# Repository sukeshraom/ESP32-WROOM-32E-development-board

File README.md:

# ESP32-WROOM-32E Development Board (Arduino UNO Form Factor)

A compact **ESP32-WROOM-32E Development Board** designed in the **Arduino UNO form factor** with a **USB Type-C** interface and **CH340C USB-to-UART** converter. The board combines the versatility of the ESP32 with the familiar Arduino UNO header layout, making it suitable for rapid prototyping and shield-based development.

[View PCB in Kicanvas](https://kicanvas.org/?repo=https%3A%2F%2Fgithub.com%2Fsamuk%2FESP32-WROOM-32E-development-board%2Ftree%2Fmain%2FKicad)
---

## Features

- ESP32-WROOM-32E module
- Arduino UNO compatible form factor
- USB Type-C connector for power and programming
- CH340C USB-to-UART interface
- Auto Reset and Auto Boot circuitry
- 3.3 V regulated power supply
- Power and User LEDs
- Standard UNO header layout
- Breakout access to ESP32 GPIOs
- Compact two-layer PCB

---

## Hardware Specifications

| Feature | Description |
|---------|-------------|
| MCU | ESP32-WROOM-32E |
| USB Interface | USB Type-C |
| USB-UART | CH340C |
| Operating Voltage | 3.3 V |
| Wireless | Wi-Fi 802.11 b/g/n, Bluetooth Classic & BLE |
| PCB Design | KiCad |

---

## Repository Contents

```
ESP32-UNO/
│
├── ESP32-module.kicad_pro
├── ESP32-module.kicad_sch
├── ESP32-module.kicad_pcb
└── README.md
```

---

## PCB Preview

```

---

## Applications

- IoT Development
- Home Automation
- Industrial Monitoring
- Sensor Interface
- Robotics
- Wireless Data Logging
- Educational Projects
- Rapid Prototyping

---

## Software

The board is compatible with:

- Arduino IDE
- PlatformIO
- ESP-IDF

Install the **ESP32 Board Package** in the Arduino IDE before programming.

---

## Manufacturing Files

This repository includes:

- KiCad Project
- Schematic
- PCB Layout
- Bill of Materials (BOM)
- Pick-and-Place File
- Designator List
- IPC Netlist

---

## License

This hardware design is provided as an open-source reference for educational, research, and prototyping purposes. You are welcome to use, modify, and improve the design while retaining appropriate attribution.

---

## Author

Designed by **Dr. Sukesh Rao M**

Department of Electronics and Communication Engineering  
NMAM Institute of Technology (NMAMIT)  
Nitte (Deemed to be University)

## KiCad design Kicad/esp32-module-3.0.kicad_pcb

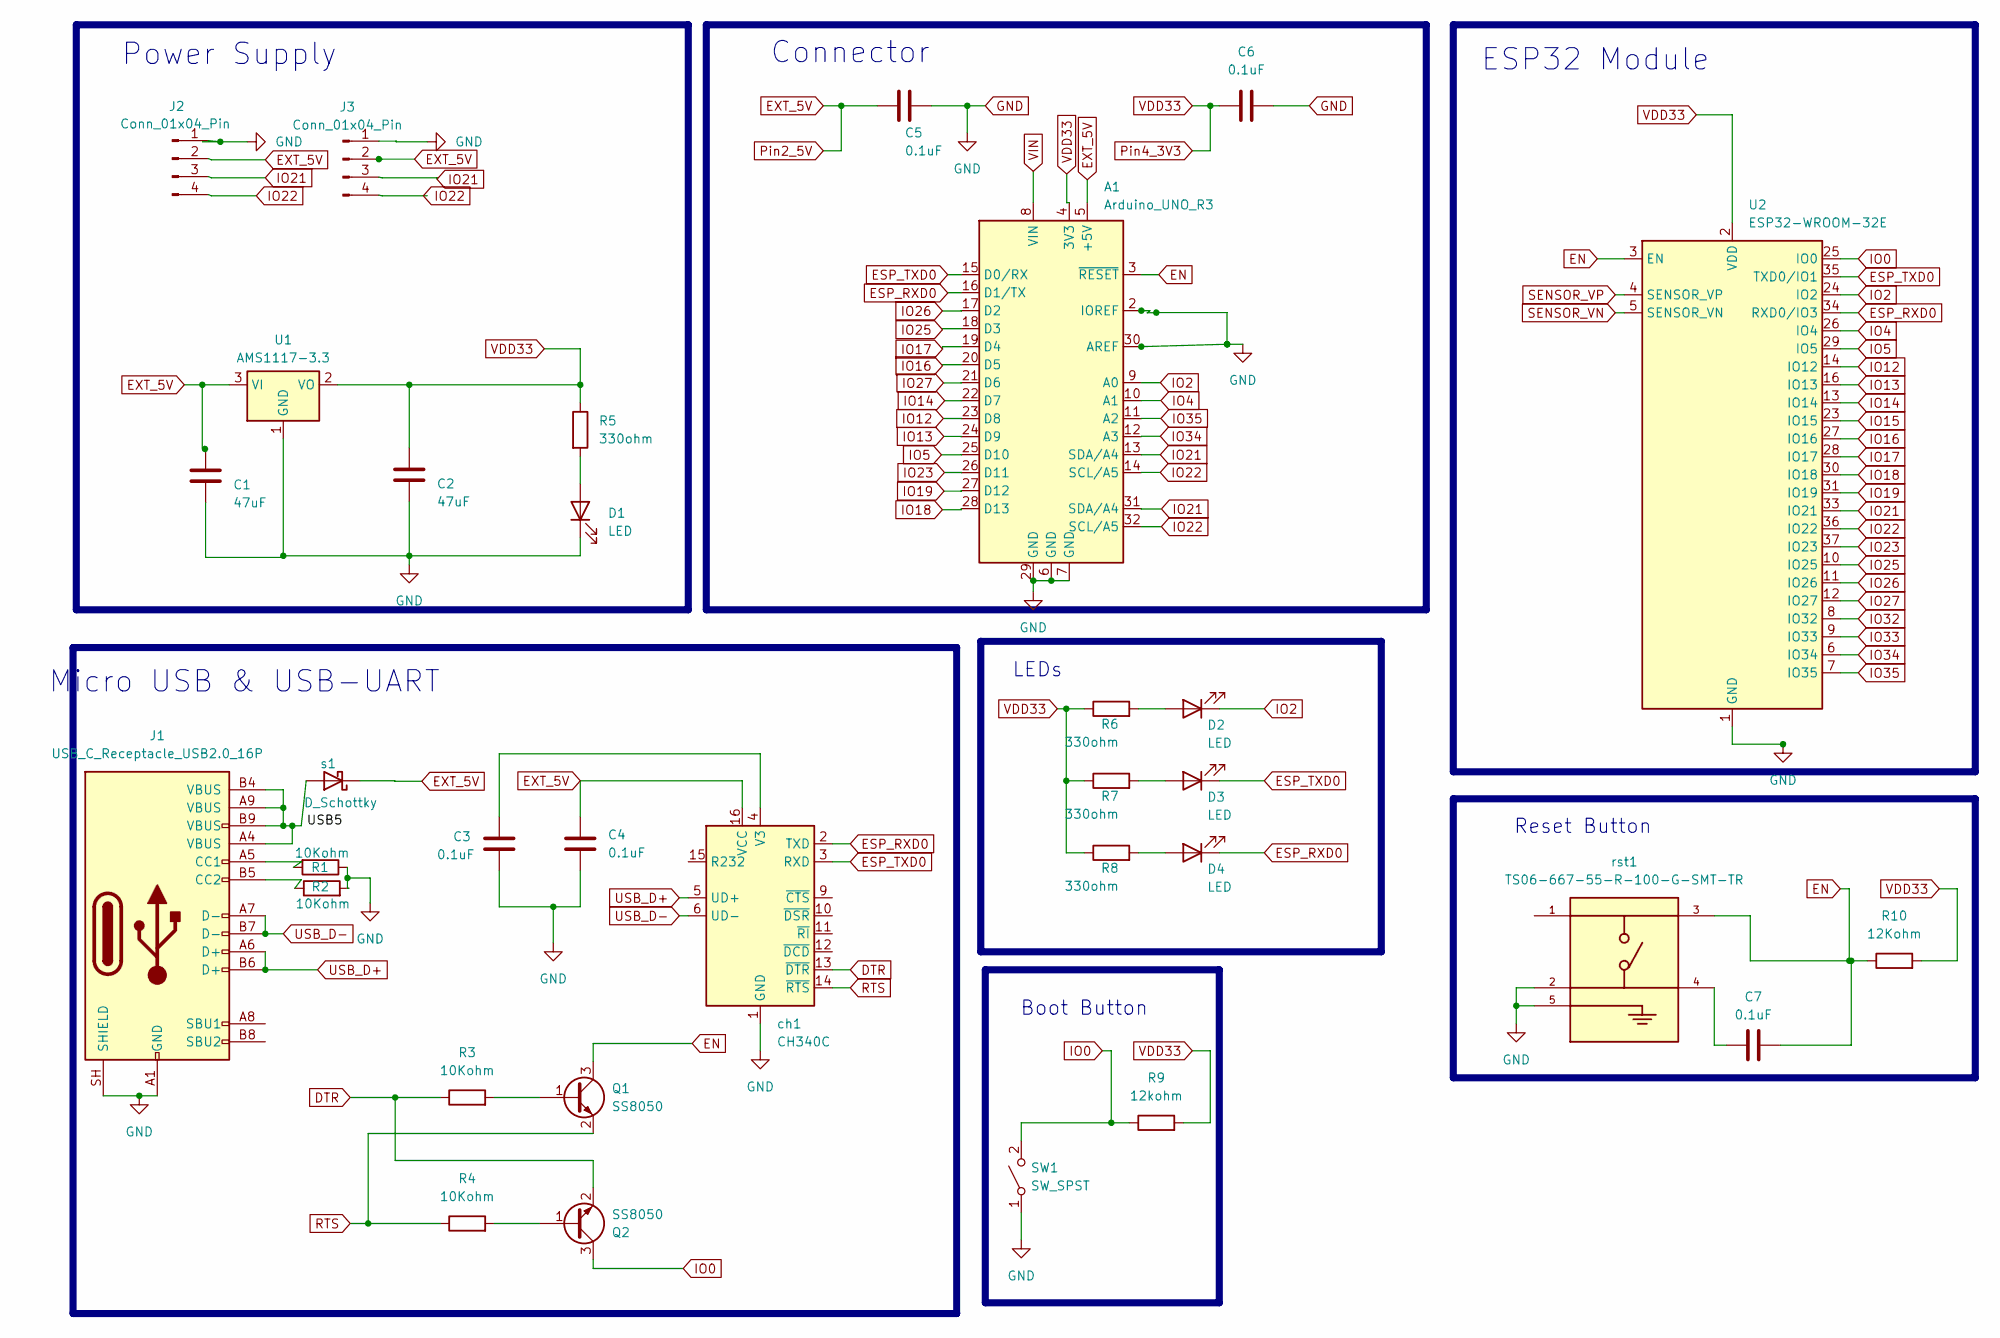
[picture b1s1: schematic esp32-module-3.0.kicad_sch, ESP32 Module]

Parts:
A1: Arduino_UNO_R3
C1, C2: 47uF; CP_Elec_5x4.4
C3, C4, C5, C6, C7: 0.1uF; C_0805_2012Metric
D1, D2, D3, D4: LED; LED_0805_2012Metric
J1: USB_C_Receptacle_USB2.0_16P; USB_C_Receptacle_GCT_USB4110
J2, J3: Conn_01x04_Pin; JST_EH_B4B-EH-A_1x04_P2.50mm_Vertical
Q1, Q2: SS8050; SOT-23
R1, R2, R3, R4: 10Kohm; R_0805_2012Metric
R5, R6, R7, R8: 330ohm; R_0805_2012Metric
R9: 12kohm; R_0805_2012Metric
R10: 12Kohm; R_0805_2012Metric
SW1: SW_SPST; SW_Tactile_SPST_NO_Straight_CK_PTS636Sx25SMTRLFS
U1: AMS1117-3.3; SOT-223-3_TabPin2
U2: ESP32-WROOM-32E; ESP32-WROOM-32D
ch1: CH340C; SOIC-16_3.9x9.9mm_P1.27mm
rst1: TS06-667-55-R-100-G-SMT-TR; SW_TS06-667-55-R-100-G-SMT-TR; PARTREV 1.0
s1: D_Schottky; D_SOD-123

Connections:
DTR: Q2.2 (E), R3.1, ch1.13 (~DTR)
EN: A1.3 (~RESET), C7.2, Q1.3 (C), R10.1, U2.3 (EN), rst1.3
ESP_RXD0: A1.16 (D1/TX), D4.1 (K), U2.34 (RXD0/IO3), ch1.2 (TXD)
ESP_TXD0: A1.15 (D0/RX), D3.1 (K), U2.35 (TXD0/IO1), ch1.3 (RXD)
EXT_5V: A1.5 (+5V), C1.1, C4.1, C5.2, J2.2, J3.2, U1.3 (VI), ch1.16 (VCC), s1.1 (K)
GND: A1.2 (IOREF), A1.6 (GND), A1.7 (GND), A1.29 (GND), A1.30 (AREF), C1.2, C2.2, C3.2, C4.2, C5.1, C6.2, D1.1 (K), J1.A1 (GND), J1.A12 (GND), J1.B1 (GND), J1.B12 (GND), J1.SH (SHIELD), J2.1, J3.1, R1.1, R2.2, SW1.1 (A), U1.1 (GND), U2.1 (GND), U2.15 (GND), U2.38 (GND), U2.39 (GND), ch1.1 (GND), rst1.2, rst1.5
IO0: Q2.3 (C), R9.1, SW1.2 (B), U2.25 (IO0)
IO2: A1.9 (A0), D2.1 (K), U2.24 (IO2)
IO4: A1.10 (A1), U2.26 (IO4)
IO5: A1.25 (D10), U2.29 (IO5)
IO12: A1.23 (D8), U2.14 (IO12)
IO13: A1.24 (D9), U2.16 (IO13)
IO14: A1.22 (D7), U2.13 (IO14)
IO15: U2.23 (IO15)
IO16: A1.20 (D5), U2.27 (IO16)
IO17: A1.19 (D4), U2.28 (IO17)
IO18: A1.28 (D13), U2.30 (IO18)
IO19: A1.27 (D12), U2.31 (IO19)
IO21: A1.13 (SDA/A4), A1.31 (SDA/A4), J2.3, J3.3, U2.33 (IO21)
IO22: A1.14 (SCL/A5), A1.32 (SCL/A5), J2.4, J3.4, U2.36 (IO22)
IO23: A1.26 (D11), U2.37 (IO23)
IO25: A1.18 (D3), U2.10 (IO25)
IO26: A1.17 (D2), U2.11 (IO26)
IO27: A1.21 (D6), U2.12 (IO27)
IO32: U2.8 (IO32)
IO33: U2.9 (IO33)
IO34: A1.12 (A3), U2.6 (IO34)
IO35: A1.11 (A2), U2.7 (IO35)
unnamed: C7.1, rst1.4
unnamed: D1.2 (A), R5.2
unnamed: D2.2 (A), R6.2
unnamed: D3.2 (A), R7.2
unnamed: D4.2 (A), R8.2
unnamed: J1.A5 (CC1), R1.2
unnamed: J1.B5 (CC2), R2.1
unnamed: Q1.1 (B), R3.2
unnamed: Q2.1 (B), R4.2
unnamed: C3.1, ch1.4 (V3)
unnamed: J1.A4 (VBUS), J1.A9 (VBUS), J1.B4 (VBUS), J1.B9 (VBUS), s1.2 (A)
Pin4_3V3: A1.4 (3V3), C2.1, C6.1, R5.1, R6.1, R7.1, R8.1, R9.2, R10.2, U1.2 (VO), U2.2 (VDD)
RTS: Q1.2 (E), R4.1, ch1.14 (~RTS)
SENSOR_VN: U2.5 (SENSOR_VN)
SENSOR_VP: U2.4 (SENSOR_VP)
USB_D+: J1.A6 (D+), J1.B6 (D+), ch1.5 (UD+)
USB_D-: J1.A7 (D-), J1.B7 (D-), ch1.6 (UD-)
VIN: A1.8 (VIN)

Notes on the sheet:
Micro USB & USB-UART
LEDs
Connector
ESP32 Module
Power Supply
Boot Button
Reset Button

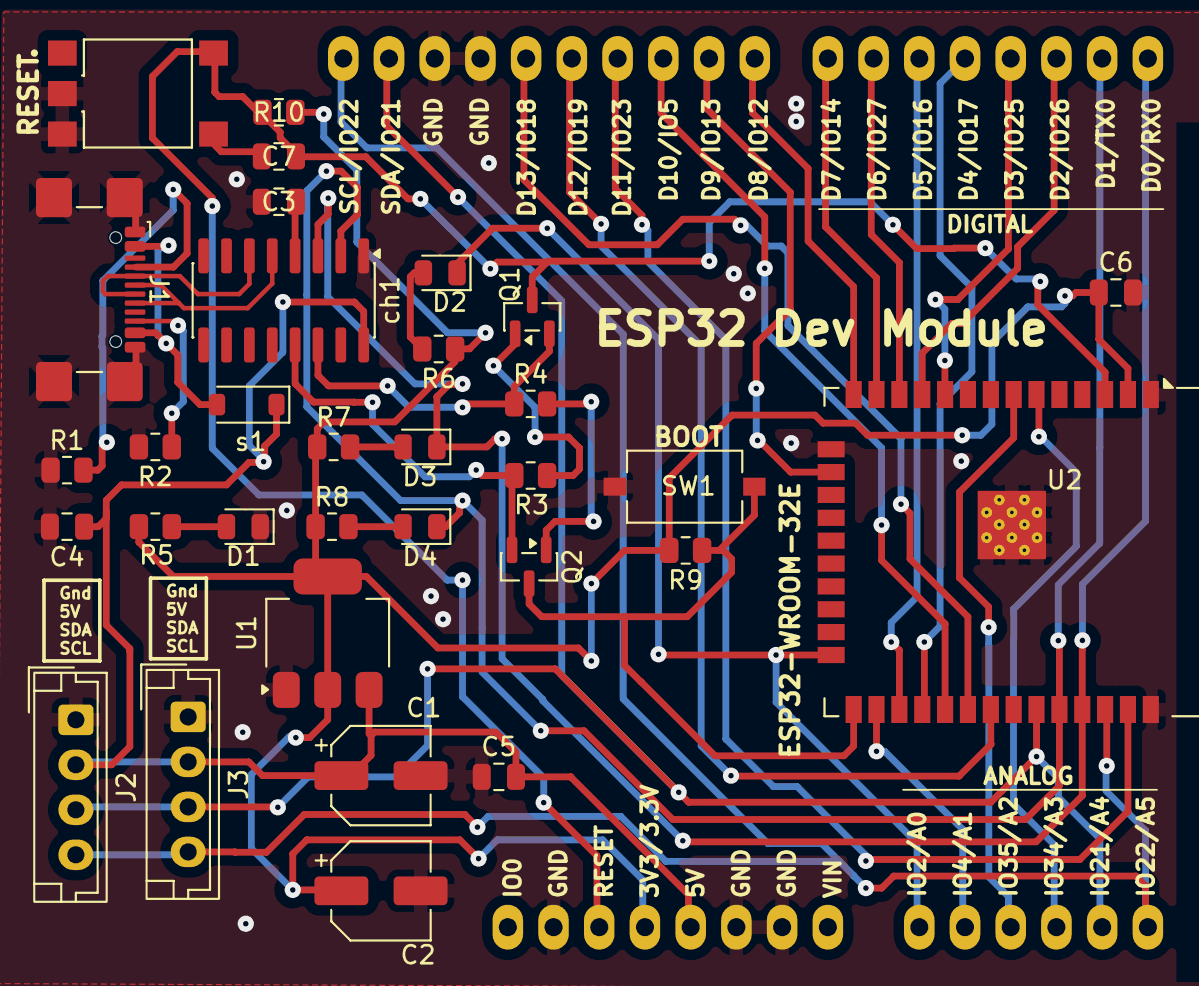
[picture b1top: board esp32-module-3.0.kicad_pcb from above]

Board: 2 copper layers, 33 parts (0 on the bottom side), 40 nets.

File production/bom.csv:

Designator,Footprint,Quantity,Value,LCSC Part #
A1,Arduino_UNO_R3,1,Arduino_UNO_R3,
"C1, C2",CP_Elec_5x4.4,2,47uF,
"C3, C4, C5, C6, C7",0805,5,0.1uF,
CH1,SOIC-16_3.9x9.9mm_P1.27mm,1,CH340C,
"D1, D2, D3, D4",0805,4,LED,
J1,USB_C_Receptacle_GCT_USB4110,1,USB_C_Receptacle_USB2.0_16P,
"J2, J3",JST_EH_B4B-EH-A_1x04_P2.50mm_Vertical,2,Conn_01x04_Pin,
"Q1, Q2",SOT-23,2,SS8050,
"R1, R2, R3, R4",0805,4,10Kohm,
"R10, R9",0805,2,12Kohm,
"R5, R6, R7, R8",0805,4,330ohm,
RST1,SW_TS06-667-55-R-100-G-SMT-TR,1,TS06-667-55-R-100-G-SMT-TR,
S1,D_SOD-123,1,D_Schottky,
SW1,SW_Tactile_SPST_NO_Straight_CK_PTS636Sx25SMTRLFS,1,SW_SPST,
U1,SOT-223-3_TabPin2,1,AMS1117-3.3,
U2,ESP32-WROOM-32D,1,ESP32-WROOM-32E,
